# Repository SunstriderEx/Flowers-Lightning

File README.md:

# Подсветка растений
Умный светильник для комнатных растений и desktop-приложение для настройки устройства по USB.

Яркость светильника зависит от внешнего освещения, чем оно ярче, тем слабее он светит, поддерживая тем самым необходимый минимальный уровень освещённости.

## Подробности
Основной элемент - STM32 Minimum system development board.

На её борту имеется часовой кварцевый резонатор, что избавляет от необходимости отдельной установки данного компонента для работы RTC.

Для работы устройства необходим внешний блок питания на 12В и ток не менее 1А.

Использованный дроссель вводит ограничение на ток, протекающий через источник(и) света. В моём случае он составил около 1А. Хотя этот компонент является необязательным, так как пульсации на частоте 30 кГц незначительны.

В качестве датчика освещённости используется фоторезистор GL5528. Для регулировки зависимости яркости от внешнего освещения в устройстве присутствует подстроечный резистор.

Для настройки устройства используется приложение под Windows, позволяющее синхронизировать время часов и указывать время сна. Интерфейс связи - USB. Скриншот программы:

При входе и выходе из режима сна яркость понижается или повышается медленно и плавно.

Для ручного перевода светильника в режим сна имеется соответствующая кнопка (устройство "проснётся" по графику).

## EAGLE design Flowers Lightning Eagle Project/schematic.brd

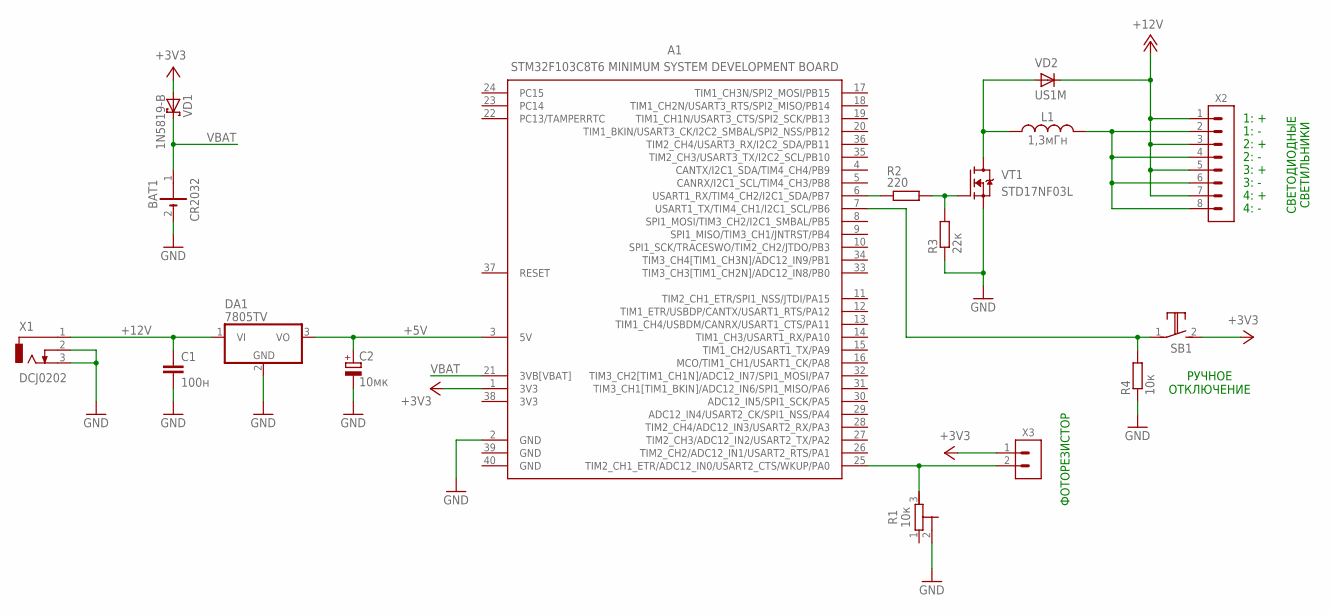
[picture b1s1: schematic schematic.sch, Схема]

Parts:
A1: STM32F103C8T6_MINIMUM_SYSTEM_DEVELOPMENT_BOARD
BAT1: CR2032; CR2032HOLDER
C1: 100н; C025-025X050
C2: 10мк; E2-4
DA1: 7805TV; TO220V
L1: 1,3мГн; INDUCTOR-2.5MH
R1: 10к; TRIMMER
R2: 220; 0207/10
R3: 22к; 0207/10
R4: 10к; 0207/10
SB1: PBS-10B-2
VD1: 1N5819-B; DO41-7.6
VD2: US1M; DO-214AC
VT1: STD17NF03L; DPAK
X1: DCJ0202
X2: TERMINALS_BLOCK_8PIN
X3: TERMINALS_BLOCK_2PIN

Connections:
3V3: A1.38 (3V3)
+3V3: A1.1 (3V3), SB1.2 (NO), VD1.A, X3.1
+5V: A1.3 (5V), C2.+, DA1.3 (VO)
+12V: C1.1, DA1.1 (VI), VD2.C, X1.1, X2.1, X2.3, X2.5, X2.7
DRAIN: L1.1, VD2.A, VT1.D
GND: A1.2 (GND), A1.39 (GND), A1.40 (GND), BAT1.2 (-), C1.2, C2.-, DA1.2 (GND), R1.2 (S), R3.1, R4.1, VT1.S, X1.2, X1.3
unnamed: A1.7 (USART1_TX/TIM4_CH1/I2C1_SCL/PB6), R4.2, SB1.1 (COM)
unnamed: R2.2, R3.2, VT1.G
unnamed: L1.2, X2.2, X2.4, X2.6, X2.8
unnamed: A1.25 (TIM2_CH1_ETR/ADC12_IN0/USART2_CTS/WKUP/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), R1.3 (E), X3.2
unnamed: A1.6 (USART1_RX/TIM4_CH2/I2C1_SDA/PB7), R2.1
VBAT: A1.21 (3VB[VBAT]), BAT1.1 (+), VD1.C

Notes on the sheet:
ФОТОРЕЗИСТОР
СВЕТОДИОДНЫЕ СВЕТИЛЬНИКИ
1: +
1: -
2: +
2: -
3: +
3: -
4: +
4: -
РУЧНОЕ ОТКЛЮЧЕНИЕ

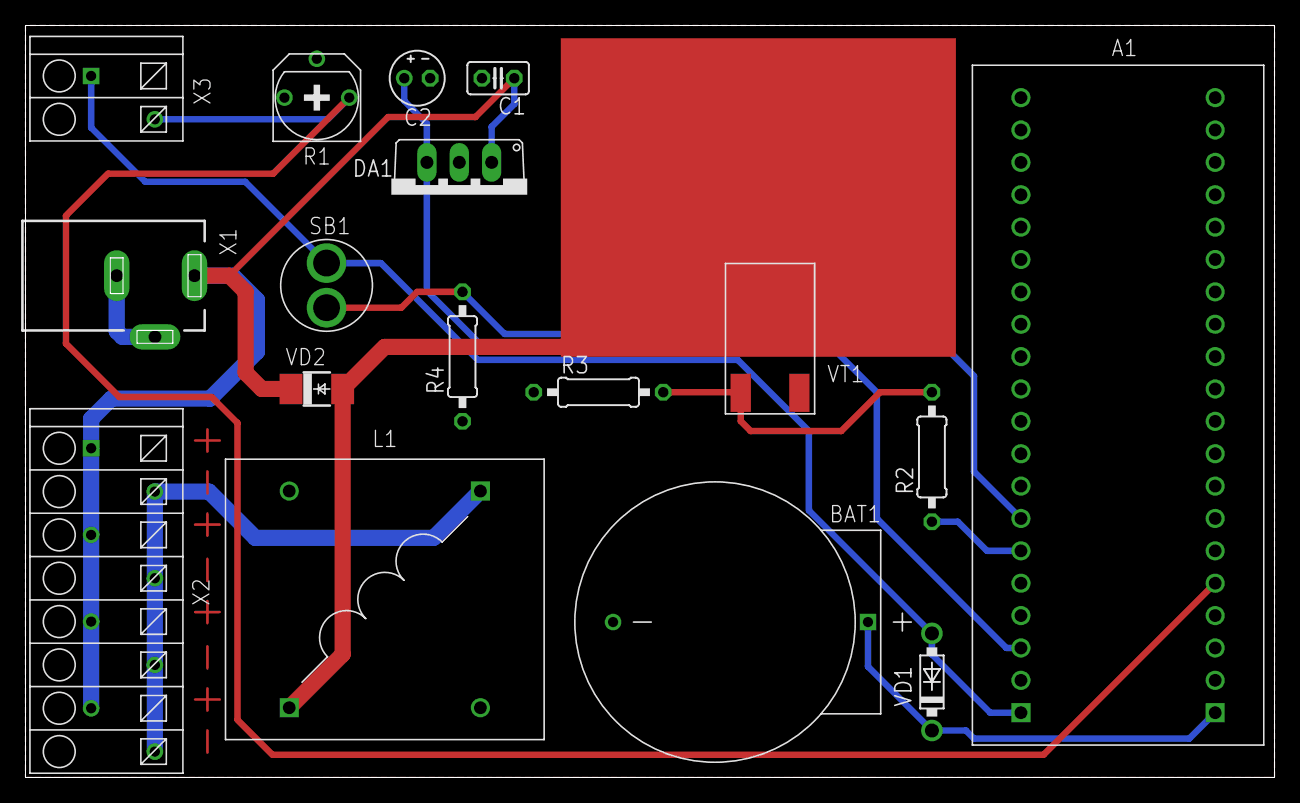
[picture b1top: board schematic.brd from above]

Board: 2 copper layers, 98.0 x 59.0 mm, 17 parts (0 on the bottom side), 11 nets.

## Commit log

2018-04-05 Files upload
2018-04-07 STM32 board data
2018-04-07 Keil uVision Project upload
